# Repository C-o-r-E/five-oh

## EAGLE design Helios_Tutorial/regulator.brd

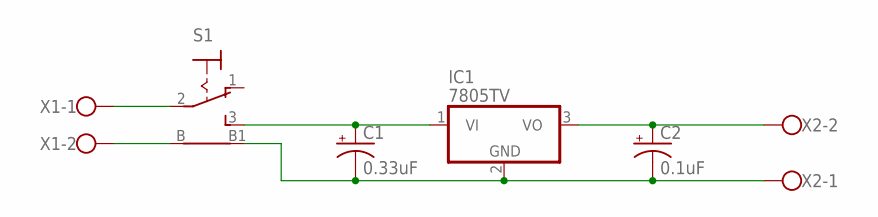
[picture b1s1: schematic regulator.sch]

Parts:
C1: 0.33uF; E3,5-8
C2: 0.1uF; E2-4
IC1: 7805TV; TO220V
S1: 9070-1W
X1, X2: W237-102

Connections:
GND: C1.-, C2.-, IC1.2 (GND), S1.B1, X2.1
unnamed: S1.2, X1.1
unnamed: S1.B, X1.2
unnamed: C2.+, IC1.3 (VO), X2.2
unnamed: C1.+, IC1.1 (VI), S1.3 (S)

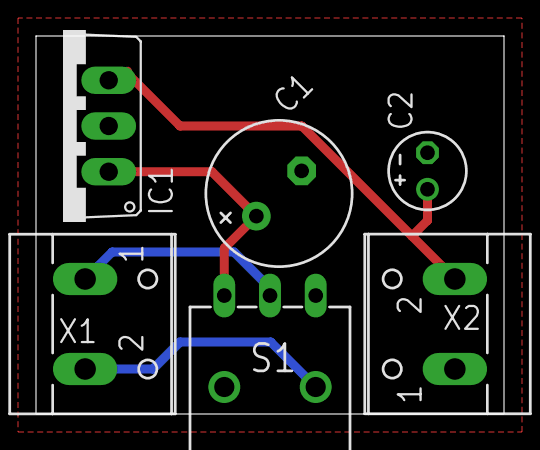
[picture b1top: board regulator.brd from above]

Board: 2 copper layers, 26.0 x 21.0 mm, 6 parts (0 on the bottom side), 5 nets.

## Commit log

2014-07-23 git this project on version control
